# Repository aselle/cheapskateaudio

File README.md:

# CheapAudio

## Introduction

The purpose of this project is to create a set of hardware and software that allows you to do your own speakers that involve active crossovers.

Software is extremely rough, mostly used for my own purposes. Use at your own risk, what contributions are welcome. 

## Components

### Current hardware

#### CheapDSP V3 - ADAU1452 based DSP board w/ RP2040 USB sound card

#### CheapAMP V2 - AD TI TAS 5754M Amp Modified to have compatible connector w/ V3

### Older Hardware

#### CheapDSP - ADAU1701 based DSP board

#### CheapAMP - TI TAS 5754M Amp

#### CheapSPDIF - SPDIF to i2s supported by wolfsen chip

One thing that I've done uniquely with these is that I have used skidl to design the circuit using python script. This has the downside that there is no hardware schematic, only a PCB layout.

### Software
  * dspserver - A server that runs on a esp8266 that allows you to upload new firmwares for your DSP, control volume, etc. It also implements Sigma Studio TCP/IP interface so you can use the Sigma Studio tools w/o the USB interface
  * React - The start of an interface for manipulating the DSP through the web
  * Tools - Utility scripts to convert various SigmaStudio 
  * Measuring - NumPy script that can measure response curve from calibrated Microphone

## License

This project is licensed under Apache 2.0 for the softawre and CERN Open Hardware Licence Version 2 – Permissive for the hardware.

## Warranty

There is no warranty implied or otherwise (see license file for details).
This is not a ready to use and tested product. Use at your own risk.

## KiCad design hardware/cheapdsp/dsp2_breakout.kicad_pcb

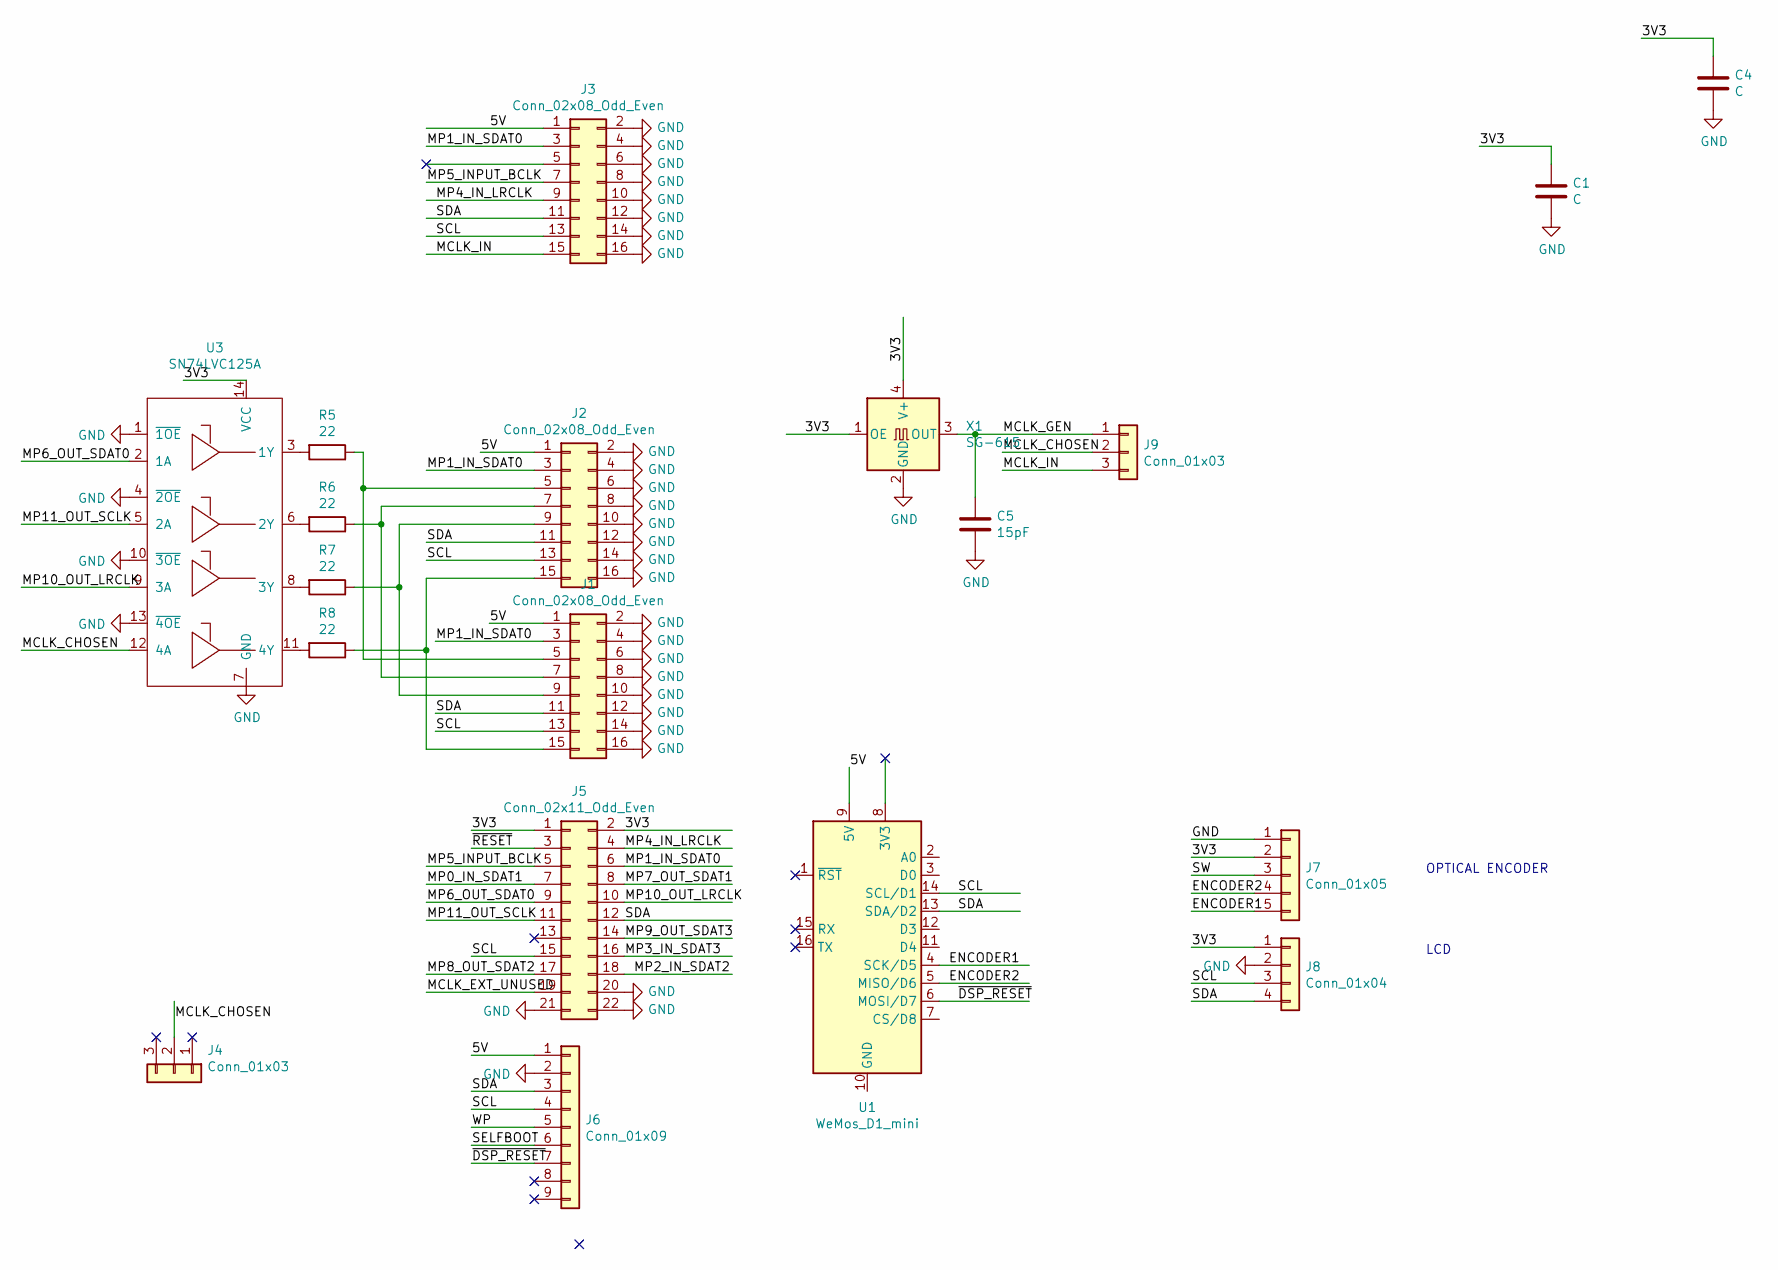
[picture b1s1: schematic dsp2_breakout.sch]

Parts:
C1, C4: C; C_0805_2012Metric_Pad1.15x1.40mm_HandSolder
C5: 15pF; C_0805_2012Metric_Pad1.15x1.40mm_HandSolder
J1, J2, J3: Conn_02x08_Odd_Even; IDC-Header_2x08_P2.54mm_Vertical
J4: Conn_01x03; PinSocket_1x03_P2.54mm_Vertical
J5: Conn_02x11_Odd_Even; PinSocket_2x11_P2.54mm_Vertical
J6: Conn_01x09; PinSocket_1x09_P2.54mm_Vertical
J7: Conn_01x05; PinHeader_1x05_P2.54mm_Vertical
J8: Conn_01x04; PinHeader_1x04_P2.54mm_Vertical
J9: Conn_01x03; PinHeader_1x03_P2.54mm_Vertical
R5, R6, R7, R8: 22; R_0805_2012Metric_Pad1.15x1.40mm_HandSolder
U1: WeMos_D1_mini; WEMOS_D1_mini_light
U3: SN74LVC125A; SOIC-14_3.9x8.7mm_P1.27mm
X1: SG-615; 7.0x5.0_SMD_OSCILLATOR_HCOMS_TTLCUSTOM

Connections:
/3V3: C1.1, C4.1, J5.1, J5.2, J7.2, J8.1, U3.14 (VCC), X1.1 (OE), X1.4 (V+)
/5V: J1.1, J2.1, J3.1, J6.1, U1.9 (5V)
/ENCODER1: J7.5, U1.4 (SCK/D5)
/ENCODER2: J7.4, U1.5 (MISO/D6)
/MCLK_CHOSEN: J4.2, J9.2, U3.12 (4A)
/MCLK_EXT_UNUSED: J5.19
/MCLK_GEN: C5.1, J9.1, X1.3 (OUT)
/MCLK_IN: J3.15, J9.3
/MP0_IN_SDAT1: J5.7
/MP1_IN_SDAT0: J1.3, J2.3, J3.3, J5.6
/MP2_IN_SDAT2: J5.18
/MP3_IN_SDAT3: J5.16
/MP4_IN_LRCLK: J3.9, J5.4
/MP5_INPUT_BCLK: J3.7, J5.5
/MP6_OUT_SDAT0: J5.9, U3.2 (1A)
/MP7_OUT_SDAT1: J5.8
/MP8_OUT_SDAT2: J5.17
/MP9_OUT_SDAT3: J5.14
/MP10_OUT_LRCLK: J5.10, U3.9 (3A)
/MP11_OUT_SCLK: J5.11, U3.5 (2A)
/SCL: J1.13, J2.13, J3.13, J5.15, J6.4, J8.3, U1.14 (SCL/D1)
/SDA: J1.11, J2.11, J3.11, J5.12, J6.3, J8.4, U1.13 (SDA/D2)
/SELFBOOT: J6.6
/SW: J7.3
/WP: J6.5
/~DSP_RESET: J6.7, U1.6 (MOSI/D7)
/~RESET: J5.3
GND: C1.2, C4.2, C5.2, J1.2, J1.4, J1.6, J1.8, J1.10, J1.12, J1.14, J1.16, J2.2, J2.4, J2.6, J2.8, J2.10, J2.12, J2.14, J2.16, J3.2, J3.4, J3.6, J3.8, J3.10, J3.12, J3.14, J3.16, J5.20, J5.21, J5.22, J6.2, J7.1, J8.2, U3.1 (~1OE), U3.4 (~2OE), U3.7 (GND), U3.10 (~3OE), U3.13 (~4OE), X1.2 (GND)
unnamed: J1.5, J2.5, R5.1
unnamed: J1.7, J2.7, R6.1
unnamed: J1.9, J2.9, R7.1
unnamed: J1.15, J2.15, R8.1
unnamed: R5.2, U3.3 (1Y)
unnamed: R6.2, U3.6 (2Y)
unnamed: R7.2, U3.8 (3Y)
unnamed: R8.2, U3.11 (4Y)

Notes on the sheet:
OPTICAL ENCODER
LCD

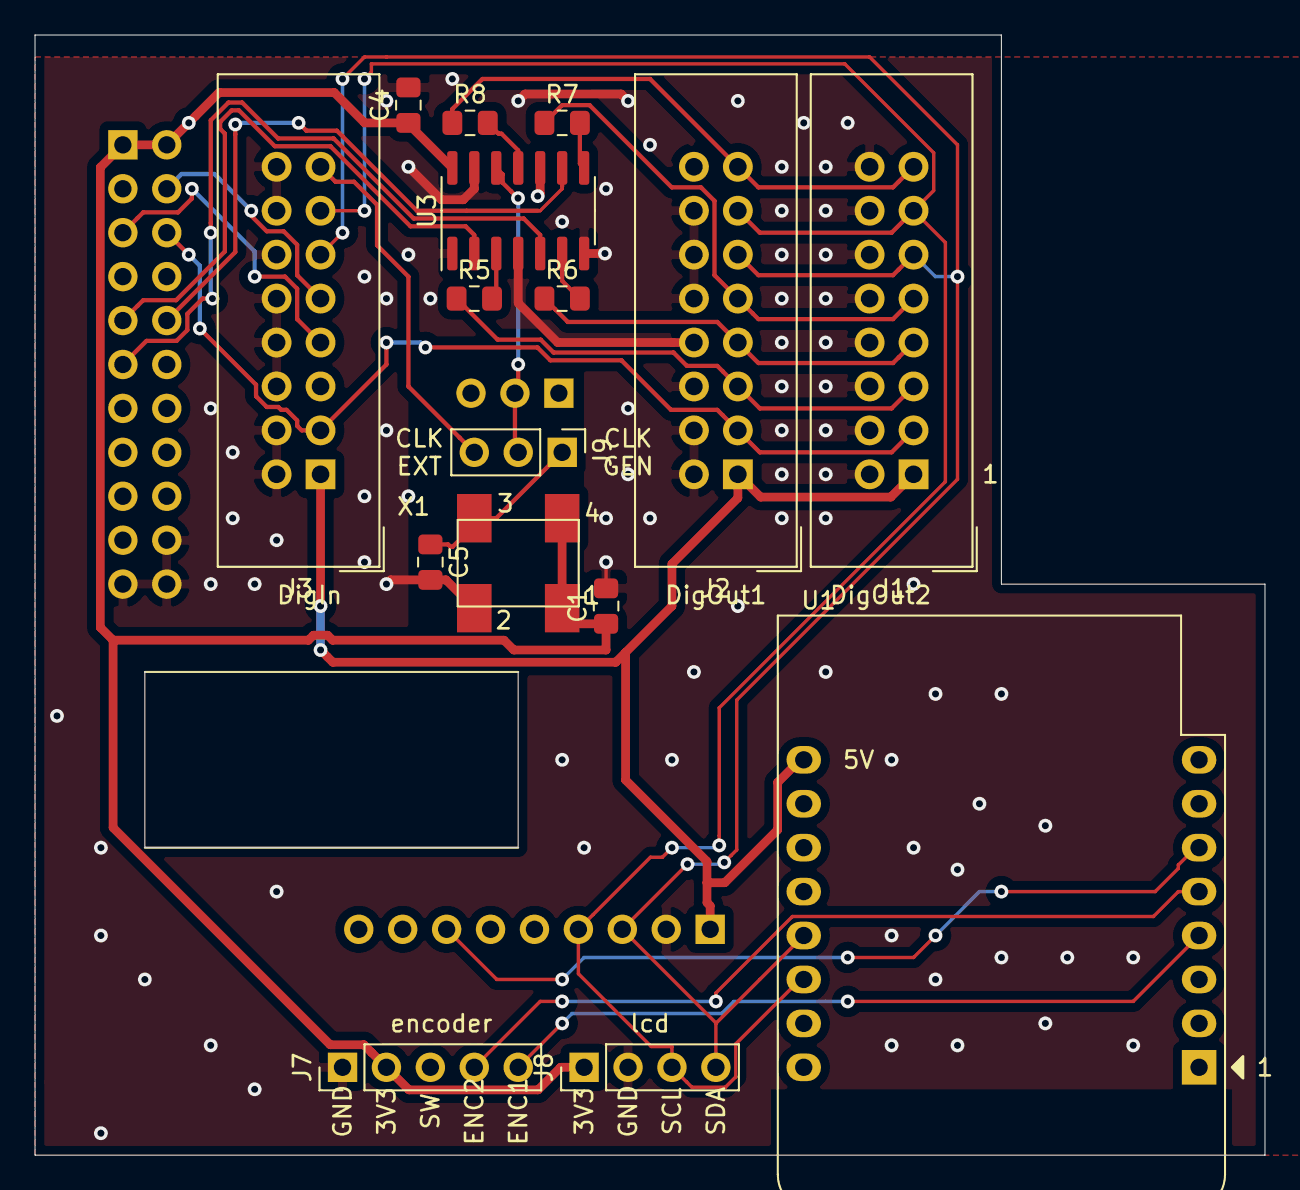
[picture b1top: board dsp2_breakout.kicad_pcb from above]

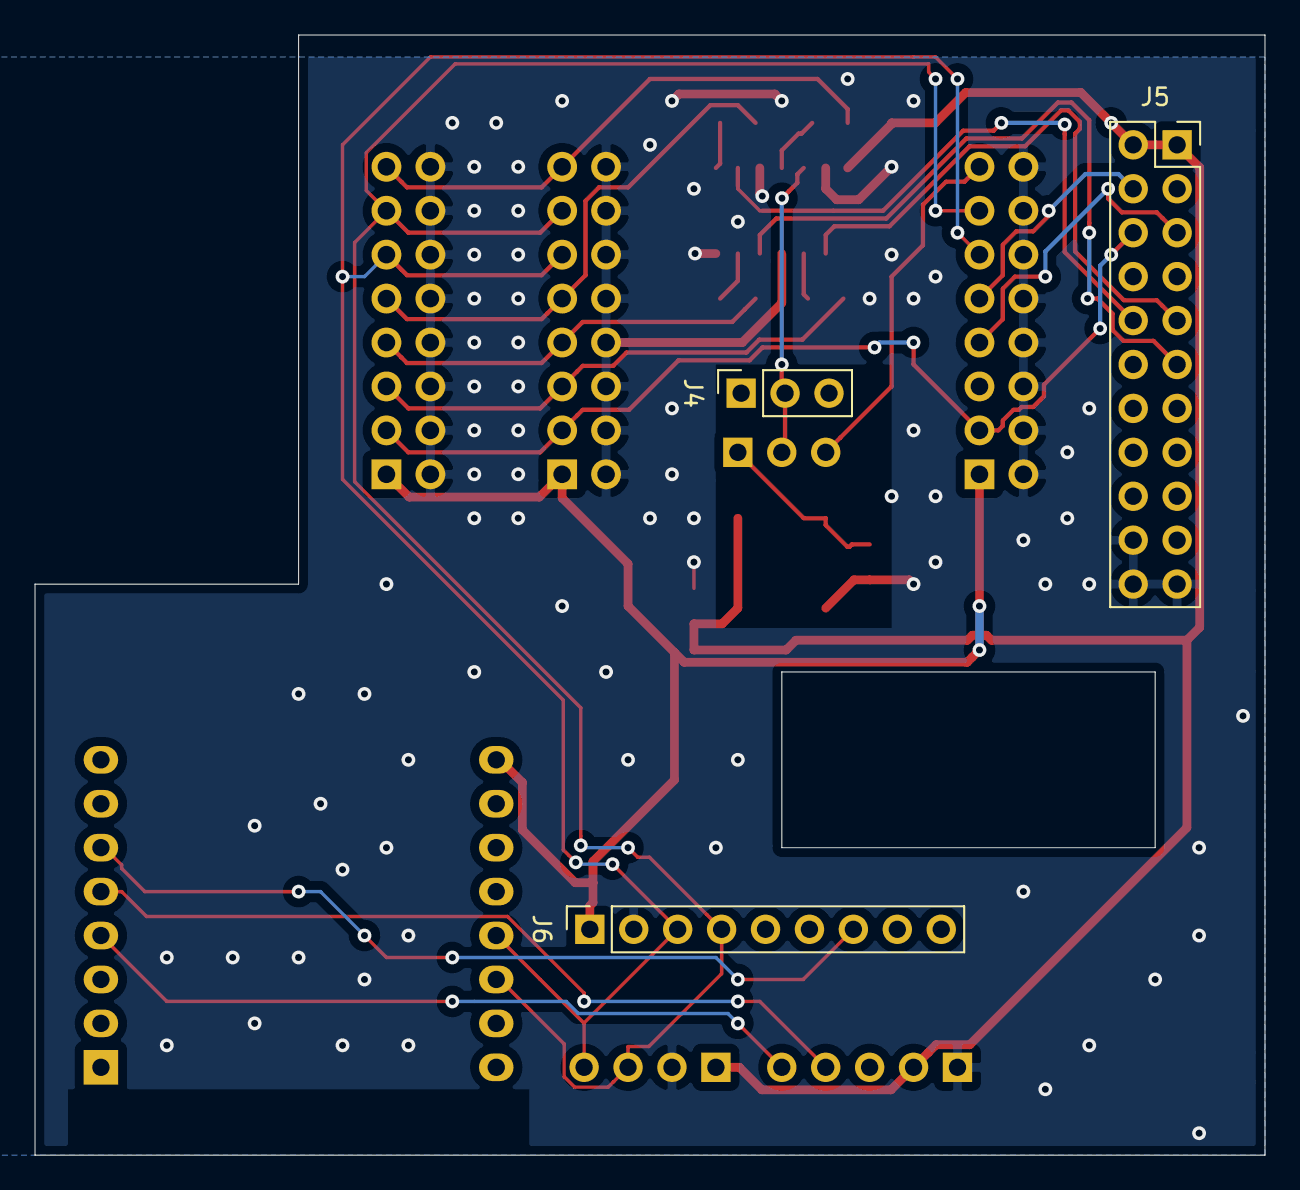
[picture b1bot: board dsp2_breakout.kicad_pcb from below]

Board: 2 copper layers, 71.1 x 64.8 mm, 19 parts (3 on the bottom side), 25 nets.

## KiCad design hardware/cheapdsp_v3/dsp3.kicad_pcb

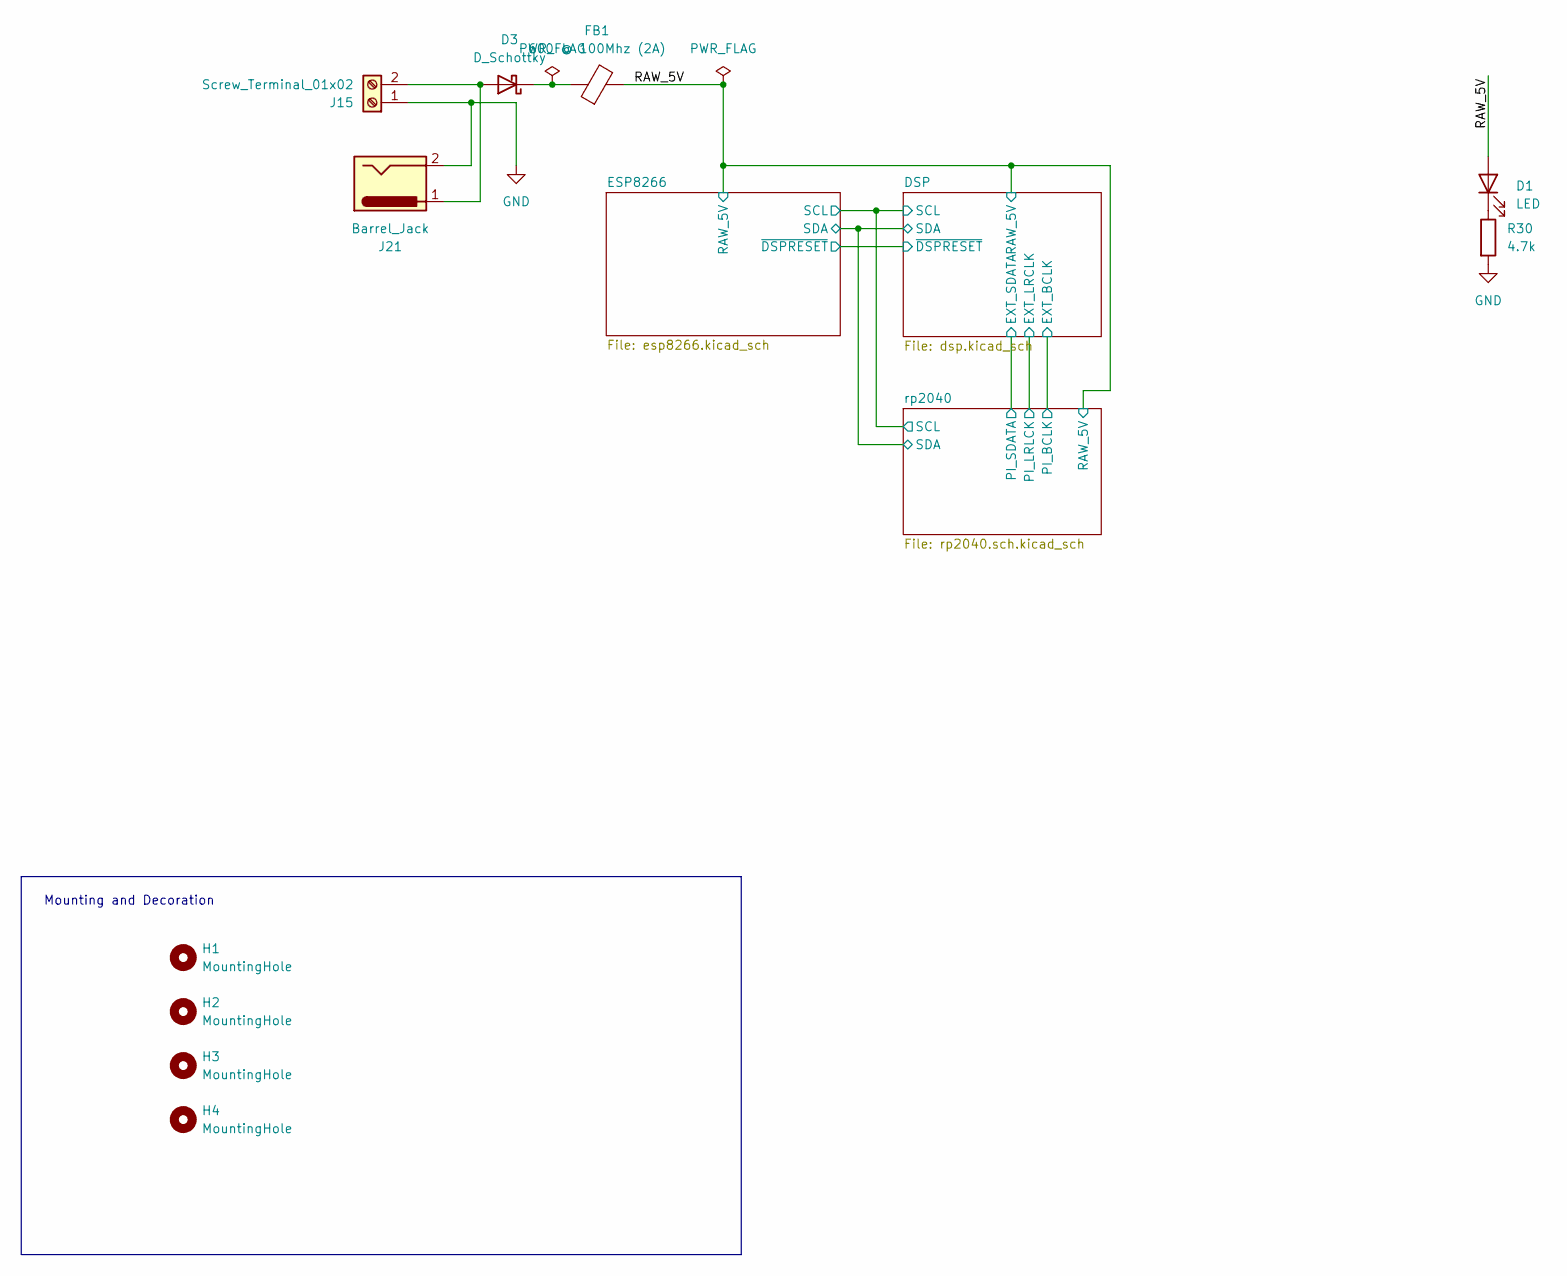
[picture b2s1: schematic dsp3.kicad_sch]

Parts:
D1: LED; LED_0805_2012Metric_Pad1.15x1.40mm_HandSolder
D3: D_Schottky; D_SMB
FB1: 600 @ 100Mhz (2A); R_0805_2012Metric
H1, H2, H3, H4: MountingHole; MountingHole_3.2mm_M3
J15: Screw_Terminal_01x02; KF301-5.0-2P
J21: Barrel_Jack; BarrelJack_Horizontal
R30: 4.7k; R_0603_1608Metric

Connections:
/RAW_5V: D1.2 (A), FB1.2; also elsewhere on the board
GND: J15.1, J21.2, R30.2; also elsewhere on the board
unnamed: D1.1 (K), R30.1
unnamed: D3.2 (A), J15.2, J21.1
unnamed: D3.1 (K), FB1.1

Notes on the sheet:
Mounting and Decoration

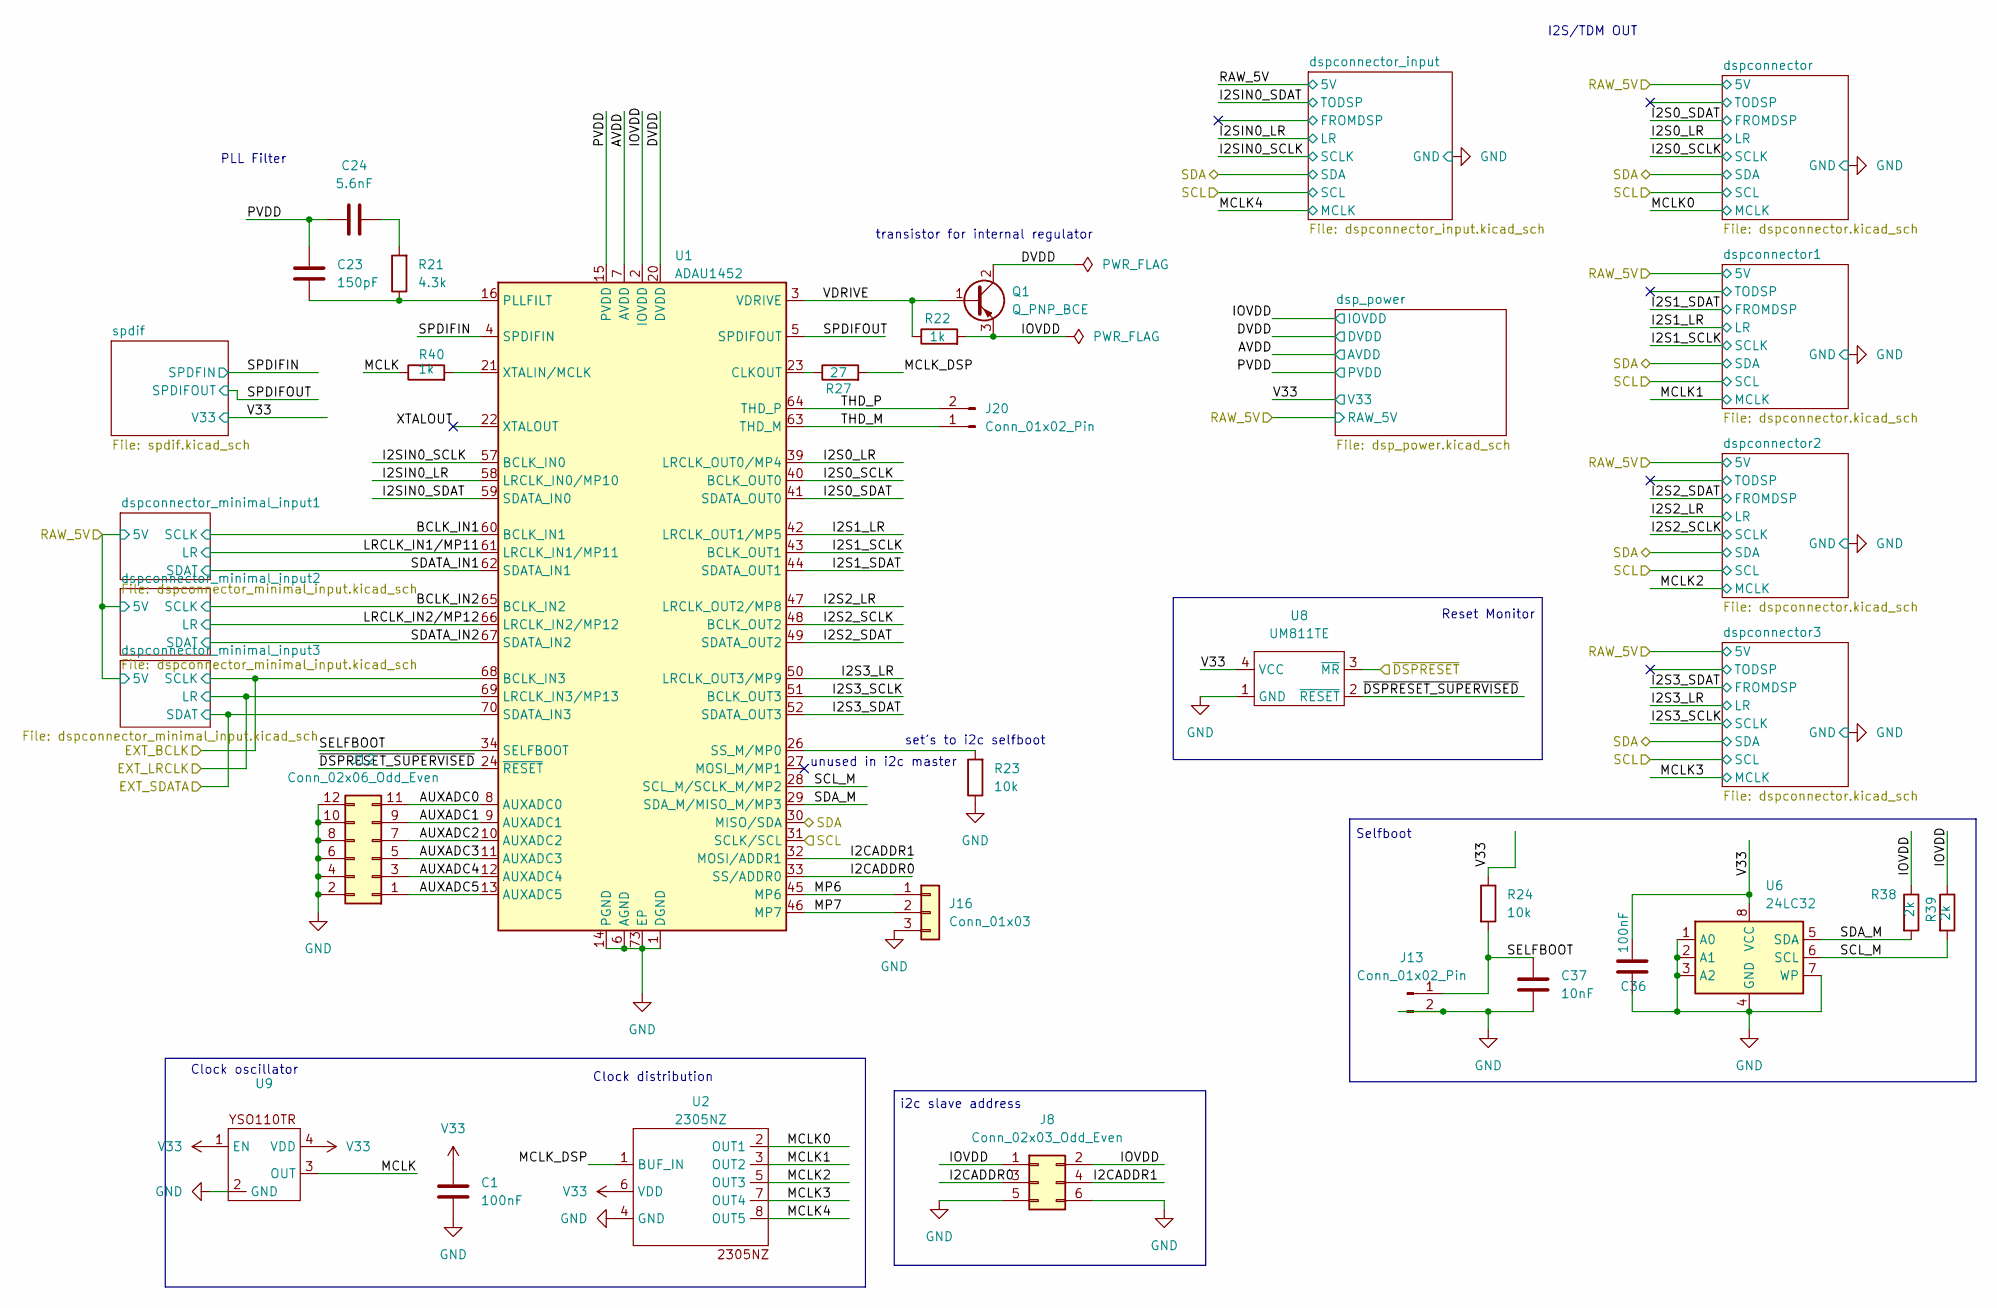
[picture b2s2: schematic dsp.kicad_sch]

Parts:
C1, C36: 100nF; C_0603_1608Metric
C23: 150pF; C_0603_1608Metric
C24: 5.6nF; C_0603_1608Metric
C37: 10nF; C_0603_1608Metric
J8: Conn_02x03_Odd_Even; PinHeader_2x03_P2.54mm_Vertical
J12: Conn_02x06_Odd_Even; PinHeader_2x06_P2.54mm_Vertical
J13, J20: Conn_01x02_Pin; PinHeader_1x02_P2.54mm_Vertical
J16: Conn_01x03; PinHeader_1x03_P2.54mm_Vertical
Q1: Q_PNP_BCE; SOT-223-3_TabPin2
R21: 4.3k; R_0603_1608Metric
R22, R40: 1k; R_0603_1608Metric
R23, R24: 10k; R_0603_1608Metric
R27: 27; R_0603_1608Metric
R38, R39: 2k; R_0603_1608Metric
U1: ADAU1452; LFCSP-72-1EP_10x10mm_P0.5mm_EP5.3x5.3mm
U2: 2305NZ; SOIC-8_5.23x5.23mm_P1.27mm
U6: 24LC32; SOIC-8_5.23x5.23mm_P1.27mm
U8: UM811TE; SOT-143
U9: YSO110TR_SMD3225

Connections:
/DSP/AUXADC0: J12.11, U1.8 (AUXADC0)
/DSP/AUXADC1: J12.9, U1.9 (AUXADC1)
/DSP/AUXADC2: J12.7, U1.10 (AUXADC2)
/DSP/AUXADC3: J12.5, U1.11 (AUXADC3)
/DSP/AUXADC4: J12.3, U1.12 (AUXADC4)
/DSP/AUXADC5: J12.1, U1.13 (AUXADC5)
/DSP/AVDD: U1.7 (AVDD); also elsewhere on the board
/DSP/BCLK_IN1: U1.60 (BCLK_IN1); also elsewhere on the board
/DSP/BCLK_IN2: U1.65 (BCLK_IN2); also elsewhere on the board
/DSP/DVDD: Q1.2 (C), U1.20 (DVDD), U1.35 (DVDD), U1.53 (DVDD), U1.71 (DVDD); also elsewhere on the board
/DSP/EXT_BCLK: U1.68 (BCLK_IN3); also elsewhere on the board
/DSP/EXT_LRCLK: U1.69 (LRCLK_IN3/MP13); also elsewhere on the board
/DSP/I2CADDR0: J8.3, U1.33 (SS/ADDR0)
/DSP/I2CADDR1: J8.4, U1.32 (MOSI/ADDR1)
/DSP/I2S0_LR: U1.39 (LRCLK_OUT0/MP4); also elsewhere on the board
/DSP/I2S0_SCLK: U1.40 (BCLK_OUT0); also elsewhere on the board
/DSP/I2S0_SDAT: U1.41 (SDATA_OUT0); also elsewhere on the board
/DSP/I2S1_LR: U1.42 (LRCLK_OUT1/MP5); also elsewhere on the board
/DSP/I2S1_SCLK: U1.43 (BCLK_OUT1); also elsewhere on the board
/DSP/I2S1_SDAT: U1.44 (SDATA_OUT1); also elsewhere on the board
/DSP/I2S2_LR: U1.47 (LRCLK_OUT2/MP8); also elsewhere on the board
/DSP/I2S2_SCLK: U1.48 (BCLK_OUT2); also elsewhere on the board
/DSP/I2S2_SDAT: U1.49 (SDATA_OUT2); also elsewhere on the board
/DSP/I2S3_LR: U1.50 (LRCLK_OUT3/MP9); also elsewhere on the board
/DSP/I2S3_SCLK: U1.51 (BCLK_OUT3); also elsewhere on the board
/DSP/I2S3_SDAT: U1.52 (SDATA_OUT3); also elsewhere on the board
/DSP/I2SIN0_LR: U1.58 (LRCLK_IN0/MP10); also elsewhere on the board
/DSP/I2SIN0_SCLK: U1.57 (BCLK_IN0); also elsewhere on the board
/DSP/I2SIN0_SDAT: U1.59 (SDATA_IN0); also elsewhere on the board
/DSP/LRCLK_IN1/MP11: U1.61 (LRCLK_IN1/MP11); also elsewhere on the board
/DSP/LRCLK_IN2/MP12: U1.66 (LRCLK_IN2/MP12); also elsewhere on the board
/DSP/MCLK: R40.1, U9.3 (OUT)
/DSP/MCLK0: U2.2 (OUT1); also elsewhere on the board
/DSP/MCLK1: U2.3 (OUT2); also elsewhere on the board
/DSP/MCLK2: U2.5 (OUT3); also elsewhere on the board
/DSP/MCLK3: U2.7 (OUT4); also elsewhere on the board
/DSP/MCLK4: U2.8 (OUT5); also elsewhere on the board
/DSP/MCLK_DSP: R27.2, U2.1 (BUF_IN)
/DSP/MP6: J16.1, U1.45 (MP6)
/DSP/MP7: J16.2, U1.46 (MP7)
/DSP/SCL: U1.31 (SCLK/SCL); also elsewhere on the board
/DSP/SCL_M: R39.2, U1.28 (SCL_M/SCLK_M/MP2), U6.6 (SCL)
/DSP/SDA: U1.30 (MISO/SDA); also elsewhere on the board
/DSP/SDATA_IN1: U1.62 (SDATA_IN1); also elsewhere on the board
/DSP/SDATA_IN2: U1.67 (SDATA_IN2); also elsewhere on the board
/DSP/SDA_M: R38.2, U1.29 (SDA_M/MISO_M/MP3), U6.5 (SDA)
/DSP/SELFBOOT: C37.1, J13.1, R24.2, U1.34 (SELFBOOT)
/DSP/SPDIFIN: U1.4 (SPDIFIN); also elsewhere on the board
/DSP/SPDIFOUT: U1.5 (SPDIFOUT); also elsewhere on the board
/DSP/THD_M: J20.1, U1.63 (THD_M)
/DSP/THD_P: J20.2, U1.64 (THD_P)
/DSP/VDRIVE: Q1.1 (B), R22.1, U1.3 (VDRIVE)
/DSP/XTALOUT: U1.22 (XTALOUT)
/DSP/dspconnector_minimal_input3/SDAT: U1.70 (SDATA_IN3); also elsewhere on the board
/DSP/~DSPRESET_SUPERVISED: U1.24 (~RESET), U8.2 (~RESET)
/DSP/~DSPRESET: U8.3 (~MR); also elsewhere on the board
GND: C1.2, C36.2, C37.2, J8.5, J8.6, J12.2, J12.4, J12.6, J12.8, J12.10, J12.12, J13.2, J16.3, R23.1, U1.1 (DGND), U1.6 (AGND), U1.14 (PGND), U1.17 (DGND), U1.19 (DGND), U1.25 (DGND), U1.36 (DGND), U1.37 (DGND), U1.54 (DGND), U1.55 (DGND), U1.72 (DGND), U1.73 (EP), U2.4 (GND), U6.1 (A0), U6.2 (A1), U6.3 (A2), U6.4 (GND), U6.7 (WP), U8.1 (GND), U9.2 (GND); also elsewhere on the board
unnamed: C24.2, R21.2
unnamed: R27.1, U1.23 (CLKOUT)
unnamed: C23.2, R21.1, U1.16 (PLLFILT)
unnamed: R23.2, U1.26 (SS_M/MP0)
unnamed: R40.2, U1.21 (XTALIN/MCLK)
V33: C1.1, C23.1, C24.1, C36.1, J8.1, J8.2, Q1.3 (E), R22.2, R24.1, R38.1, R39.1, U1.2 (IOVDD), U1.15 (PVDD), U1.18 (IOVDD), U1.38 (IOVDD), U1.56 (IOVDD), U2.6 (VDD), U6.8 (VCC), U8.4 (VCC), U9.1 (EN), U9.4 (VDD); also elsewhere on the board

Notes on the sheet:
PLL Filter
set's to i2c selfboot
Clock oscillator
I2S/TDM OUT
unused in i2c master
Reset Monitor
transistor for internal regulator
Selfboot
Clock distribution
i2c slave address

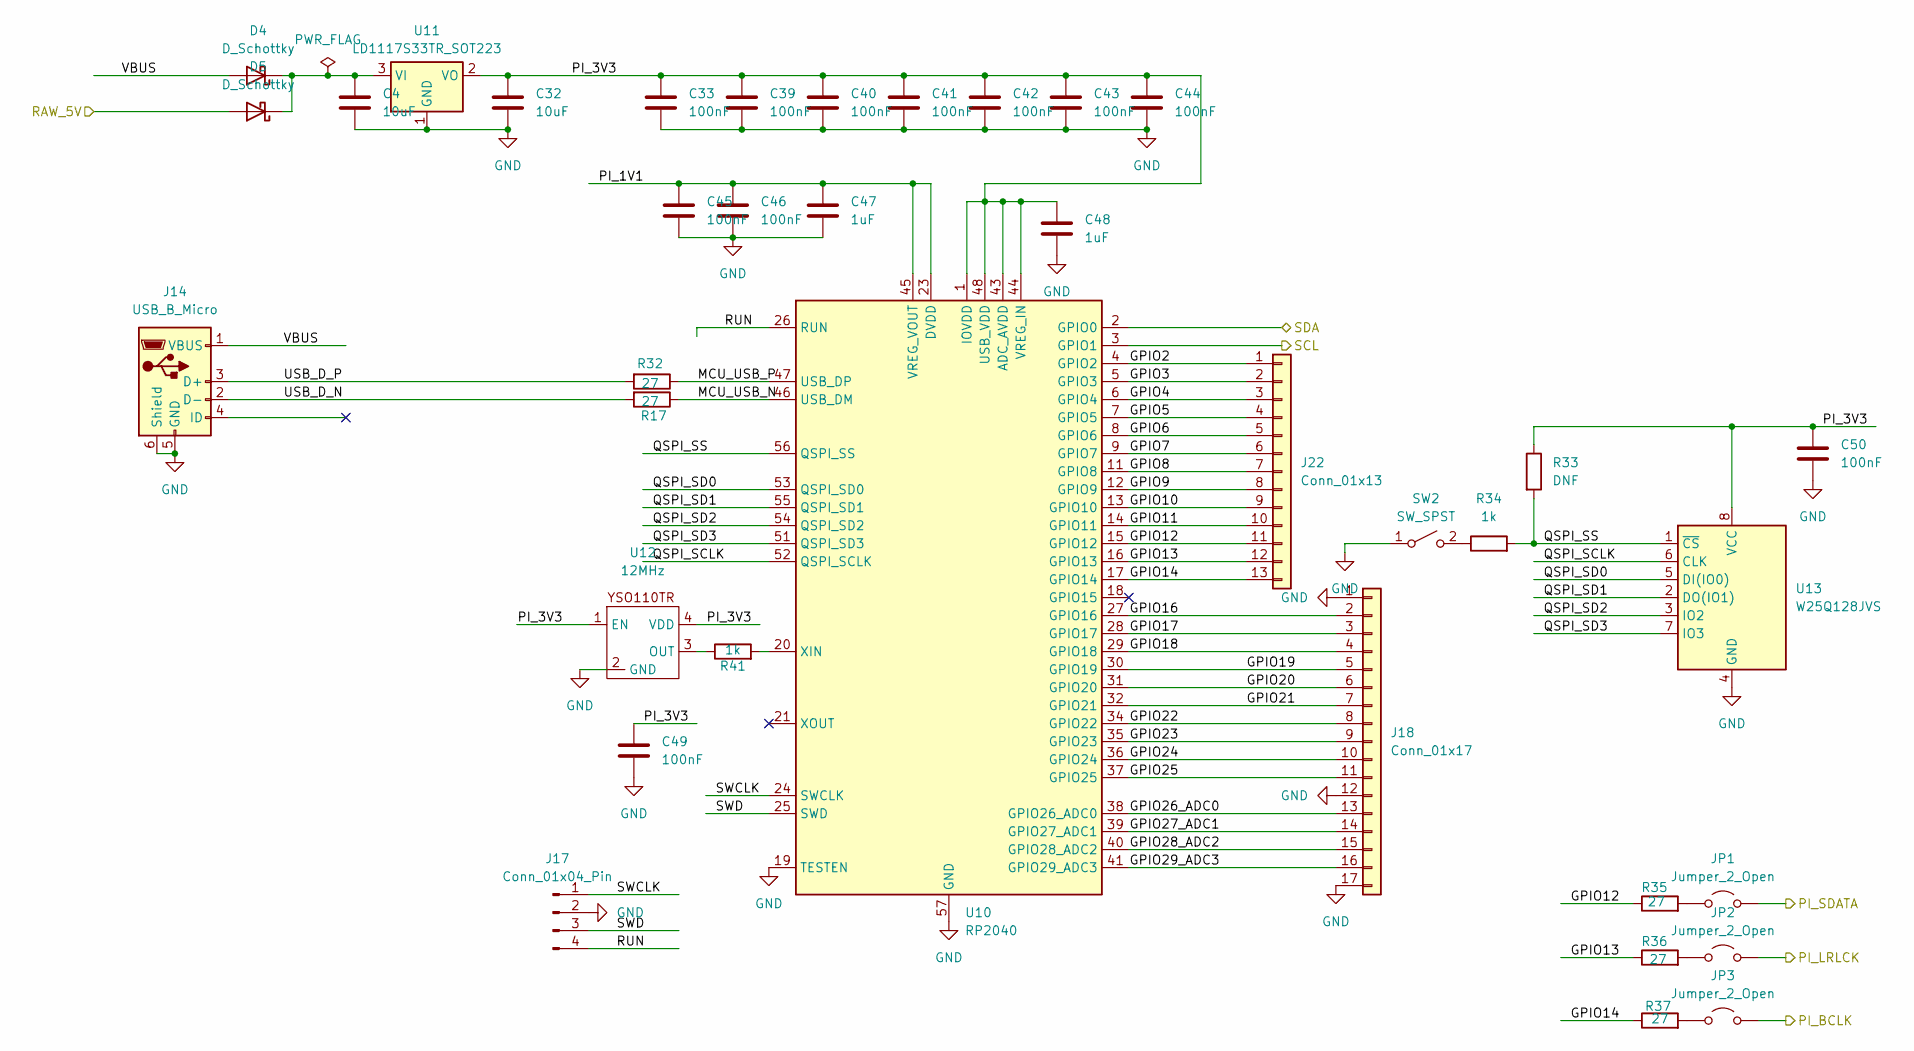
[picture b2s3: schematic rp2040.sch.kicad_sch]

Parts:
C4, C32: 10uF; C_0603_1608Metric
C33, C39, C40, C41, C42, C43, C44, C45, C46, C49, C50: 100nF; C_0603_1608Metric
C47, C48: 1uF; C_0603_1608Metric
D4, D5: D_Schottky; D_SMB
J14: USB_B_Micro; 1912111437_SHOU-HAN-MICRO5-9mmusb_C393940.pdf
J17: Conn_01x04_Pin; PinHeader_1x04_P2.54mm_Vertical
J18: Conn_01x17; PinHeader_1x17_P2.54mm_Vertical
J22: Conn_01x13; PinHeader_1x13_P2.54mm_Vertical
JP1, JP2, JP3: Jumper_2_Open; SolderJumper-2_P1.3mm_Bridged_Pad1.0x1.5mm
R17: 27; C_0603_1608Metric
R32, R35, R36, R37: 27; R_0603_1608Metric
R33: DNF; R_0603_1608Metric
R34, R41: 1k; R_0603_1608Metric
SW2: SW_SPST; SW_PUSH_6mm
U10: RP2040; QFN-56-1EP_7x7mm_P0.4mm_EP3.2x3.2mm
U11: LD1117S33TR_SOT223; SOT-223-3_TabPin2
U12: 12MHz; YSO110TR_SMD3225
U13: W25Q128JVS; SOIC-8_5.23x5.23mm_P1.27mm

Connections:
/DSP/EXT_BCLK: JP3.2 (B); also elsewhere on the board
/DSP/EXT_LRCLK: JP2.2 (B); also elsewhere on the board
/DSP/SCL: U10.3 (GPIO1); also elsewhere on the board
/DSP/SDA: U10.2 (GPIO0); also elsewhere on the board
/DSP/dspconnector_minimal_input3/SDAT: JP1.2 (B); also elsewhere on the board
/RAW_5V: D5.2 (A); also elsewhere on the board
/rp2040/GPIO2: J22.1, U10.4 (GPIO2)
/rp2040/GPIO3: J22.2, U10.5 (GPIO3)
/rp2040/GPIO4: J22.3, U10.6 (GPIO4)
/rp2040/GPIO5: J22.4, U10.7 (GPIO5)
/rp2040/GPIO6: J22.5, U10.8 (GPIO6)
/rp2040/GPIO7: J22.6, U10.9 (GPIO7)
/rp2040/GPIO8: J22.7, U10.11 (GPIO8)
/rp2040/GPIO9: J22.8, U10.12 (GPIO9)
/rp2040/GPIO10: J22.9, U10.13 (GPIO10)
/rp2040/GPIO11: J22.10, U10.14 (GPIO11)
/rp2040/GPIO12: J22.11, R35.1, U10.15 (GPIO12)
/rp2040/GPIO13: J22.12, R36.1, U10.16 (GPIO13)
/rp2040/GPIO14: J22.13, R37.1, U10.17 (GPIO14)
/rp2040/GPIO16: J18.2, U10.27 (GPIO16)
/rp2040/GPIO17: J18.3, U10.28 (GPIO17)
/rp2040/GPIO18: J18.4, U10.29 (GPIO18)
/rp2040/GPIO19: J18.5, U10.30 (GPIO19)
/rp2040/GPIO20: J18.6, U10.31 (GPIO20)
/rp2040/GPIO21: J18.7, U10.32 (GPIO21)
/rp2040/GPIO22: J18.8, U10.34 (GPIO22)
/rp2040/GPIO23: J18.9, U10.35 (GPIO23)
/rp2040/GPIO24: J18.10, U10.36 (GPIO24)
/rp2040/GPIO25: J18.11, U10.37 (GPIO25)
/rp2040/GPIO26_ADC0: J18.13, U10.38 (GPIO26_ADC0)
/rp2040/GPIO27_ADC1: J18.14, U10.39 (GPIO27_ADC1)
/rp2040/GPIO28_ADC2: J18.15, U10.40 (GPIO28_ADC2)
/rp2040/GPIO29_ADC3: J18.16, U10.41 (GPIO29_ADC3)
/rp2040/MCU_USB_N: R17.1, U10.46 (USB_DM)
/rp2040/MCU_USB_P: R32.1, U10.47 (USB_DP)
/rp2040/PI_1V1: C45.1, C46.1, C47.1, U10.23 (DVDD), U10.45 (VREG_VOUT), U10.50 (DVDD)
/rp2040/PI_3V3: C32.1, C33.1, C39.1, C40.1, C41.1, C42.1, C43.1, C44.1, C48.1, C49.1, C50.1, R33.1, U10.1 (IOVDD), U10.10 (IOVDD), U10.22 (IOVDD), U10.33 (IOVDD), U10.42 (IOVDD), U10.43 (ADC_AVDD), U10.44 (VREG_IN), U10.48 (USB_VDD), U10.49 (IOVDD), U11.2 (VO), U12.1 (EN), U12.4 (VDD), U13.8 (VCC)
/rp2040/QSPI_SCLK: U10.52 (QSPI_SCLK), U13.6 (CLK)
/rp2040/QSPI_SD0: U10.53 (QSPI_SD0), U13.5 (DI(IO0))
/rp2040/QSPI_SD1: U10.55 (QSPI_SD1), U13.2 (DO(IO1))
/rp2040/QSPI_SD2: U10.54 (QSPI_SD2), U13.3 (IO2)
/rp2040/QSPI_SD3: U10.51 (QSPI_SD3), U13.7 (IO3)
/rp2040/QSPI_SS: R33.2, R34.2, U10.56 (QSPI_SS), U13.1 (~CS)
/rp2040/RUN: J17.4, U10.26 (RUN)
/rp2040/SWCLK: J17.1, U10.24 (SWCLK)
/rp2040/SWD: J17.3, U10.25 (SWD)
/rp2040/USB_D_N: J14.2 (D-), R17.2
/rp2040/USB_D_P: J14.3 (D+), R32.2
/rp2040/VBUS: D4.2 (A), J14.1 (VBUS)
GND: C4.2, C32.2, C33.2, C39.2, C40.2, C41.2, C42.2, C43.2, C44.2, C45.2, C46.2, C47.2, C48.2, C49.2, C50.2, J14.5 (GND), J14.6 (Shield), J17.2, J18.1, J18.12, J18.17, SW2.1 (A), U10.19 (TESTEN), U10.57 (GND), U11.1 (GND), U12.2 (GND), U13.4 (GND); also elsewhere on the board
unnamed: C4.1, D4.1 (K), D5.1 (K), U11.3 (VI)
unnamed: JP1.1 (A), R35.2
unnamed: JP2.1 (A), R36.2
unnamed: JP3.1 (A), R37.2
unnamed: R34.1, SW2.2 (B)
unnamed: R41.2, U10.20 (XIN)
unnamed: R41.1, U12.3 (OUT)

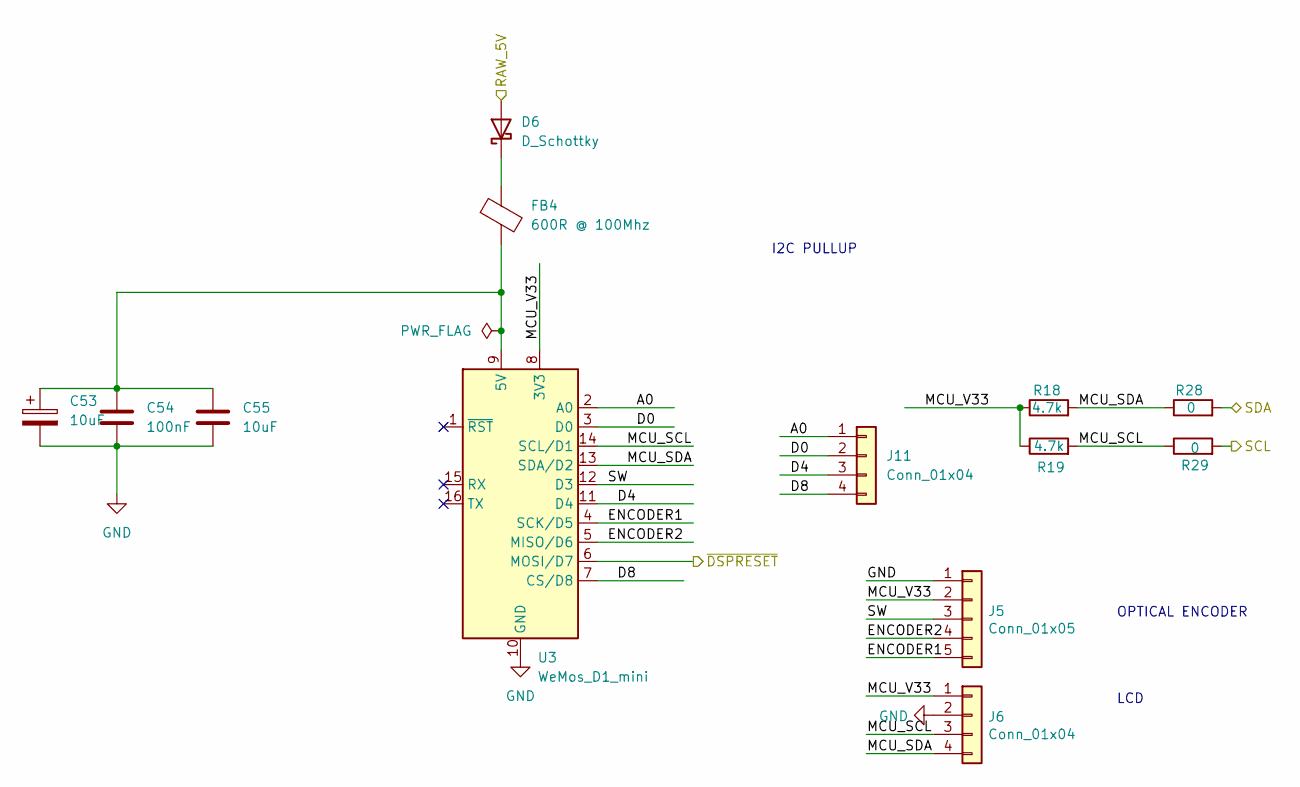
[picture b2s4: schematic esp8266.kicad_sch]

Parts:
C53: 10uF; CP_Elec_4x4.5
C54: 100nF; C_0603_1608Metric
C55: 10uF; C_0603_1608Metric
D6: D_Schottky; D_SMB
FB4: 600R @ 100Mhz; R_0805_2012Metric
J5: Conn_01x05; PinHeader_1x05_P2.54mm_Vertical
J6, J11: Conn_01x04; PinHeader_1x04_P2.54mm_Vertical
R18, R19: 4.7k; R_0603_1608Metric
R28, R29: 0; R_0603_1608Metric
U3: WeMos_D1_mini; WEMOS_D1_mini_light

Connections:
/DSP/SCL: R29.2; also elsewhere on the board
/DSP/SDA: R28.2; also elsewhere on the board
/DSP/~DSPRESET: U3.6 (MOSI/D7); also elsewhere on the board
/ESP8266/A0: J11.1, U3.2 (A0)
/ESP8266/D0: J11.2, U3.3 (D0)
/ESP8266/D4: J11.3, U3.11 (D4)
/ESP8266/D8: J11.4, U3.7 (CS/D8)
/ESP8266/ENCODER1: J5.5, U3.4 (SCK/D5)
/ESP8266/ENCODER2: J5.4, U3.5 (MISO/D6)
/ESP8266/MCU_SCL: J6.3, R19.2, R29.1, U3.14 (SCL/D1)
/ESP8266/MCU_SDA: J6.4, R18.2, R28.1, U3.13 (SDA/D2)
/ESP8266/MCU_V33: J5.2, J6.1, R18.1, R19.1, U3.8 (3V3)
/ESP8266/SW: J5.3, U3.12 (D3)
/RAW_5V: D6.2 (A); also elsewhere on the board
GND: C53.2, C54.2, C55.2, J5.1, J6.2, U3.10 (GND); also elsewhere on the board
unnamed: D6.1 (K), FB4.1
unnamed: C53.1, C54.1, C55.1, FB4.2, U3.9 (5V)

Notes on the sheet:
OPTICAL ENCODER
I2C PULLUP
LCD

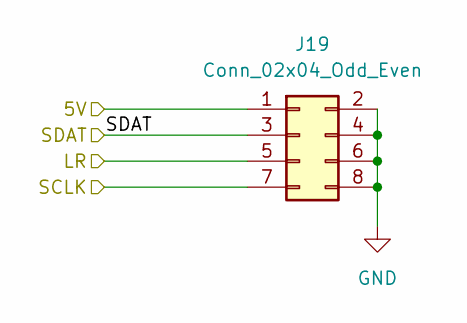
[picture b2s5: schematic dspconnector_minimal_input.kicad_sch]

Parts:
J19: Conn_02x04_Odd_Even; PinHeader_2x04_P2.54mm_Vertical

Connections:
/DSP/EXT_BCLK: J19.7; also elsewhere on the board
/DSP/EXT_LRCLK: J19.5; also elsewhere on the board
/DSP/dspconnector_minimal_input3/SDAT: J19.3; also elsewhere on the board
/RAW_5V: J19.1; also elsewhere on the board
GND: J19.2, J19.4, J19.6, J19.8; also elsewhere on the board

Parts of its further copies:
J9, J10: Conn_02x04_Odd_Even; PinHeader_2x04_P2.54mm_Vertical

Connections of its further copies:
/DSP/BCLK_IN1: J10.7; also elsewhere on the board
/DSP/BCLK_IN2: J9.7; also elsewhere on the board
/DSP/LRCLK_IN1/MP11: J10.5; also elsewhere on the board
/DSP/LRCLK_IN2/MP12: J9.5; also elsewhere on the board
/DSP/SDATA_IN1: J10.3; also elsewhere on the board
/DSP/SDATA_IN2: J9.3; also elsewhere on the board
/RAW_5V: J9.1, J10.1; also elsewhere on the board
GND: J9.2, J9.4, J9.6, J9.8, J10.2, J10.4, J10.6, J10.8; also elsewhere on the board
